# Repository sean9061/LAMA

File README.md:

# LAMA

LAMA は、左右分割・トラックボール付きのワイヤレス自作キーボードです。[roBa](https://github.com/kumamuk-git/roBa)（[keyball](https://github.com/Yowkees/keyball/) に影響を受けた分割キーボード）を改造して作りました。ファームウェアは [ZMK](https://zmk.dev/) です。

## 特徴

- **左右分割・カラムスタッガード配列。** roBa の両端（小指側）に1列ずつキーを増やしている
- **右手に 25mm のトラックボール**（センサーは PMW3610）。ボールを動かすとマウスのレイヤーに自動で切り替わる
- **Bluetooth（BLE）で無線接続。** マイコンは左右とも Seeed Studio XIAO nRF52840 Plus
- **単3電池1本で動く。** 昇圧回路（TPS61221）で 3.3V にしている。電源スイッチ付き。電池の残量はファームウェアからは測れない
- 左手にロータリーエンコーダ（EC12）を付けられる（押し込みスイッチは未配線）
- **ZMK Studio に対応。** 右手を USB でつなぐと、ブラウザからキーマップを変えられる
- XIAO の RGB LED で Bluetooth の接続状態を表示する
- キーマップは Mac で使う前提（英数/かな、⌘、Mission Control、Spotlight など）

## キーマップ

| レイヤー | 入り方 | 内容 |
|---|---|---|
| BASE | — | 文字の入力 |
| FUNCTION | 右手親指の ⏎ を長押し | F1〜F13、明るさ・音楽・音量、スクリーンショット（⇧⌘4 / ⇧⌘5） |
| NUM | 左手親指の Space を長押し | テンキー（左手）と記号（右手） |
| ARROW | 左手親指の かな を長押し | 矢印・Home/End、タブの切り替え、ブラウザの戻る/進む |
| MOUSE | トラックボールを動かす（自動） | 右手の J/K/L が左/中/右クリック |
| SCROLL | I を長押し | トラックボールでスクロール |
| SYSTEM | 左手親指の 英数 を長押し | Bluetooth の接続先の切り替え・消去、ブートローダー |

英数・かな のキーは、タップすると BASE レイヤーに戻ってから英数・かなを送ります。キーマップの詳しい説明とピン配置は [doc/firmware.md](doc/firmware.md) にあります。

[doc/keymap.html](doc/keymap.html) は、ダウンロードしてブラウザで開くと、押したキーが光る配置図です（`python3 doc/keymap_gen.py` で keymap から作り直せます）。

## ファームウェア

### 入手する

push すると、GitHub Actions がファームウェアをビルドします（[.github/workflows/build.yml](.github/workflows/build.yml)）。Actions のページで最新の実行を開き、Artifacts からダウンロードすると、次の3つが入っています。

| ファイル | 書き込む先 |
|---|---|
| `LAMA_R-seeeduino_xiao_ble-zmk.uf2` | 右手（central。トラックボール側） |
| `LAMA_L-seeeduino_xiao_ble-zmk.uf2` | 左手（peripheral） |
| `settings_reset-seeeduino_xiao_ble-zmk.uf2` | 左右の接続をやり直したいとき（下記） |

自分のキーマップでビルドしたいときは、このリポジトリを fork して `config/LAMA.keymap` を書き換え、fork 先で Actions を有効にしてください。

### 書き込む

1. XIAO を USB でパソコンにつなぎ、リセットボタンをすばやく2回押す
2. USB ドライブが出てくるので、uf2 をそこへコピーする。コピーが終わると自動で再起動する
3. もう片方も同じように書き込む

左右がつながらなくなったときは、左右それぞれに `settings_reset` を書き込んでから、もう一度 `LAMA_L` / `LAMA_R` を書き込みます。パソコン側に残っている Bluetooth の登録も削除してください。

### キーマップを変える

- **ZMK Studio を使う:** 右手を USB でつなぎ、[ZMK Studio](https://zmk.studio/) で変える。変更はキーボードに保存され、ファームウェアのキーマップより優先される
- **ファイルを書き換える:** `config/LAMA.keymap` を編集して push する。Studio で保存したキーマップが残っていると反映されないので、そのときは Studio で「Restore Stock Settings」を実行する

キー配置図（`keymap-drawer/`）は、Actions の「Draw Keymap」を手動で実行すると作り直されます。

## ハードウェア

| ディレクトリ | 内容 |
|---|---|
| `pcb/v2/roBa_L/`・`pcb/v2/roBa_R/` | LAMA の基板（KiCad、左手・右手）。roBa の v2 基板をもとに、増設した列・XIAO nRF52840 Plus・昇圧回路を加えている |
| `pcb/` のそのほか | `pcb/v1/` は roBa の旧版の基板。PMW3610 のブレークアウト基板、エンコーダの延長基板、シンボルとフットプリントのライブラリ（`_kicad_symbols/`・`_kicad_footprints/`・`KiCADv6/`） |

組み立ての手順とケースは、roBa 本家の[ビルドガイド](https://github.com/kumamuk-git/roBa/blob/main/doc/v3/buildguide_v3.md)と[ケースのデータ](https://github.com/kumamuk-git/roBa/tree/main/case)を参考にしてください。LAMA で足した部品（増設した列のスイッチ、昇圧回路、単3電池の端子）は、このガイドには載っていません。

KiCad でライブラリを読むには、環境変数 `ROBA_FP`（`pcb/_kicad_footprints`）、`ROBA_SYMBOL`（`pcb/_kicad_symbols`）、`ROBA_V6_FP`（`pcb/KiCADv6/footprints.pretty`）、`ROBA_V6_SYM`（`pcb/KiCADv6`）を設定してください（KiCad の「設定 → パスの設定」）。

## リポジトリの構成

```
.
├── boards/shields/LAMA/   ZMK のシールド定義(ピン配置・物理レイアウト・左右の設定)
├── config/                キーマップ(LAMA.keymap)・物理レイアウト(LAMA.json)・west.yml
├── keymap-drawer/         キー配置図(LAMA.svg)
├── doc/keymap.html        押したキーが光るキー配置図(doc/keymap_gen.py で生成)
├── build.yaml             GitHub Actions でビルドする組み合わせ
├── pcb/                   基板(上記)
├── doc/                   ファームウェアの説明・写真
└── zephyr/module.yml      このリポジトリを ZMK のモジュールとして読ませる設定
```

## クレジット

- [roBa](https://github.com/kumamuk-git/roBa)（kumamuk-git）— LAMA のもとになったキーボード。LAMA の基板・ファームウェアの設定・フットプリントとシンボルのライブラリは roBa のものを改造している。組み立てとケースも roBa 本家の資料を参照
- [keyball](https://github.com/Yowkees/keyball/) — roBa が影響を受けたキーボード
- [zmk-config-roBa](https://github.com/kumamuk-git/zmk-config-roBa) / [zmk-pmw3610-driver](https://github.com/kumamuk-git/zmk-pmw3610-driver) — ZMK の設定とトラックボールのドライバ
- [zmk-rgbled-widget](https://github.com/caksoylar/zmk-rgbled-widget) — XIAO の LED で接続状態を表示する
- [keymap-drawer](https://github.com/caksoylar/keymap-drawer) — キー配置図の生成

## ライセンス

[GPLv3](LICENSE)。[roBa](https://github.com/kumamuk-git/roBa)（GPLv3）をもとにした派生プロジェクトです。

## English

LAMA is a wireless split keyboard with a 25 mm trackball, based on [roBa](https://github.com/kumamuk-git/roBa). It adds an extra pinky column on each side, has a power switch and an optional EC12 rotary encoder on the left half, runs [ZMK](https://zmk.dev/) on two Seeed Studio XIAO nRF52840 Plus boards, is powered by a single AA battery per half, and supports ZMK Studio. GitHub Actions builds the firmware on every push. See [doc/firmware.md](doc/firmware.md) for the pin assignments and keymap details. Licensed under GPLv3.

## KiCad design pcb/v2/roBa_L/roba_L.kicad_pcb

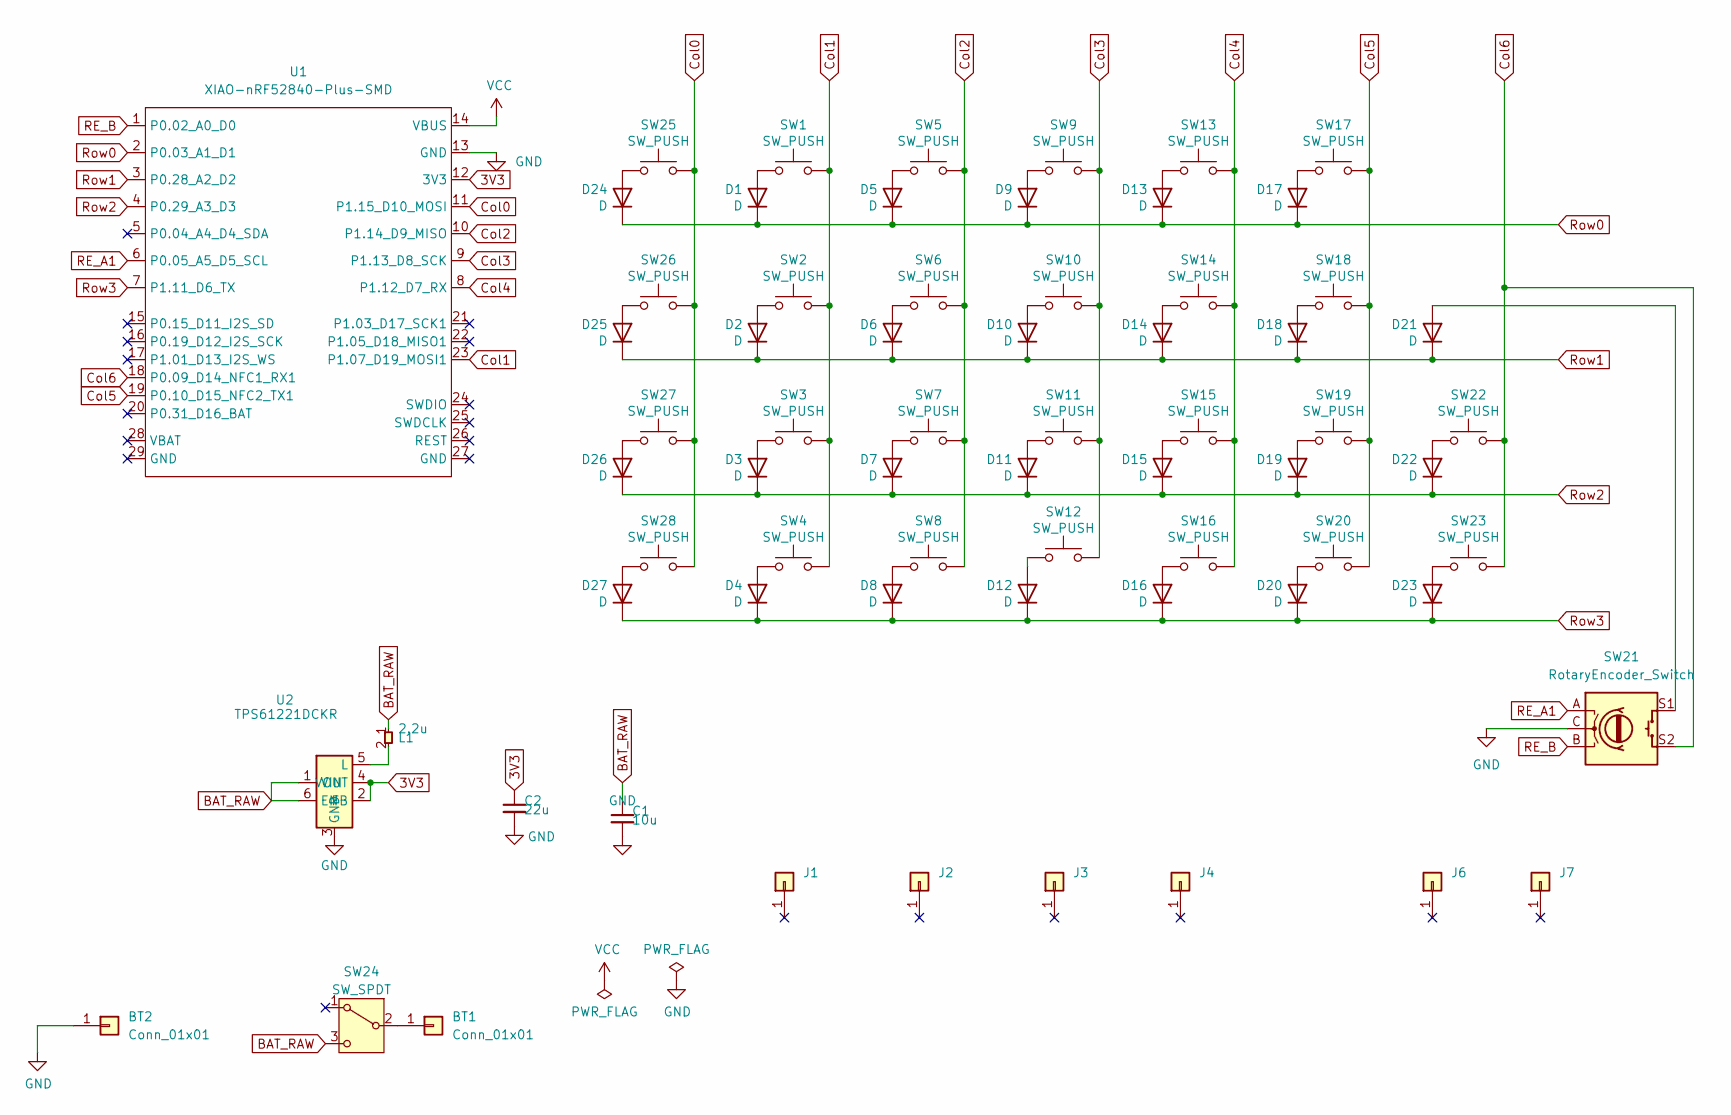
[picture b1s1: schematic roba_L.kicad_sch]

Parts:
BT1, BT2: Conn_01x01; BatteryLead_Plus
C1: 10u; C_0805_2012Metric
C2: 22u; C_0805_2012Metric
D1, D2, D3, D4, D5, D6, D7, D8, D9, D10, D11, D12, D13, D14, D15, D16, D17, D18, D19, D20, D21, D22, D23, D24, D25, D26, D27: D; Diode_SMD
J1, J2, J3, J4, J6, J7: Conn_01x01-Connector_Generic; MountingHole_4.3mm_M4
L1: 2.2u; C_0805_2012Metric
SW1, SW2, SW3, SW4, SW5, SW6, SW7, SW8, SW9, SW10, SW11, SW12, SW13, SW14, SW15, SW16, SW17, SW18, SW19, SW20, SW22, SW23, SW25, SW26, SW27, SW28: SW_PUSH; SW_MX_Choc
SW21: RotaryEncoder_Switch; SW_MX_EC12
SW24: SW_SPDT; TGSW_MSK-12D19
U1: XIAO-nRF52840-Plus-SMD
U2: TPS61221DCKR; DCK0006A

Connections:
3V3: C2.1, U1.12 (3V3), U2.2 (FB), U2.4 (VOUT)
BAT_RAW: C1.1, L1.1, SW24.3 (C), U2.1 (VIN), U2.6 (EN)
Col0: SW25.1, SW26.1, SW27.1, SW28.1, U1.11 (P1.15_D10_MOSI)
Col1: SW1.1, SW2.1, SW3.1, SW4.1, U1.23 (P1.07_D19_MOSI1)
Col2: SW5.1, SW6.1, SW7.1, SW8.1, U1.10 (P1.14_D9_MISO)
Col3: SW9.1, SW10.1, SW11.1, SW12.1, U1.9 (P1.13_D8_SCK)
Col4: SW13.1, SW14.1, SW15.1, SW16.1, U1.8 (P1.12_D7_RX)
Col5: SW17.1, SW18.1, SW19.1, SW20.1, U1.19 (P0.10_D15_NFC2_TX1)
Col6: SW21.S2, SW22.1, SW23.1, U1.18 (P0.09_D14_NFC1_RX1)
GND: BT2.1 (Pin_1_1), C1.2, C2.2, SW21.C, U1.13 (GND), U2.3 (GND)
unnamed: BT1.1 (Pin_1_1), SW24.2 (B)
unnamed: D1.2 (A), SW1.2
unnamed: D2.2 (A), SW2.2
unnamed: D3.2 (A), SW3.2
unnamed: D4.2 (A), SW4.2
unnamed: D5.2 (A), SW5.2
unnamed: D6.2 (A), SW6.2
unnamed: D7.2 (A), SW7.2
unnamed: D8.2 (A), SW8.2
unnamed: D9.2 (A), SW9.2
unnamed: D10.2 (A), SW10.2
unnamed: D11.2 (A), SW11.2
unnamed: D12.2 (A), SW12.2
unnamed: D13.2 (A), SW13.2
unnamed: D14.2 (A), SW14.2
unnamed: D15.2 (A), SW15.2
unnamed: D16.2 (A), SW16.2
unnamed: D17.2 (A), SW17.2
unnamed: D18.2 (A), SW18.2
unnamed: D19.2 (A), SW19.2
unnamed: D20.2 (A), SW20.2
unnamed: D21.2 (A), SW21.S1
unnamed: D22.2 (A), SW22.2
unnamed: D23.2 (A), SW23.2
unnamed: D24.2 (A), SW25.2
unnamed: D25.2 (A), SW26.2
unnamed: D26.2 (A), SW27.2
unnamed: D27.2 (A), SW28.2
unnamed: L1.2, U2.5 (L)
RE_A1: SW21.A, U1.6 (P0.05_A5_D5_SCL)
RE_B: SW21.B, U1.1 (P0.02_A0_D0)
Row0: D1.1 (K), D5.1 (K), D9.1 (K), D13.1 (K), D17.1 (K), D24.1 (K), U1.2 (P0.03_A1_D1)
Row1: D2.1 (K), D6.1 (K), D10.1 (K), D14.1 (K), D18.1 (K), D21.1 (K), D25.1 (K), U1.3 (P0.28_A2_D2)
Row2: D3.1 (K), D7.1 (K), D11.1 (K), D15.1 (K), D19.1 (K), D22.1 (K), D26.1 (K), U1.4 (P0.29_A3_D3)
Row3: D4.1 (K), D8.1 (K), D12.1 (K), D16.1 (K), D20.1 (K), D23.1 (K), D27.1 (K), U1.7 (P1.11_D6_TX)
VCC: U1.14 (VBUS)

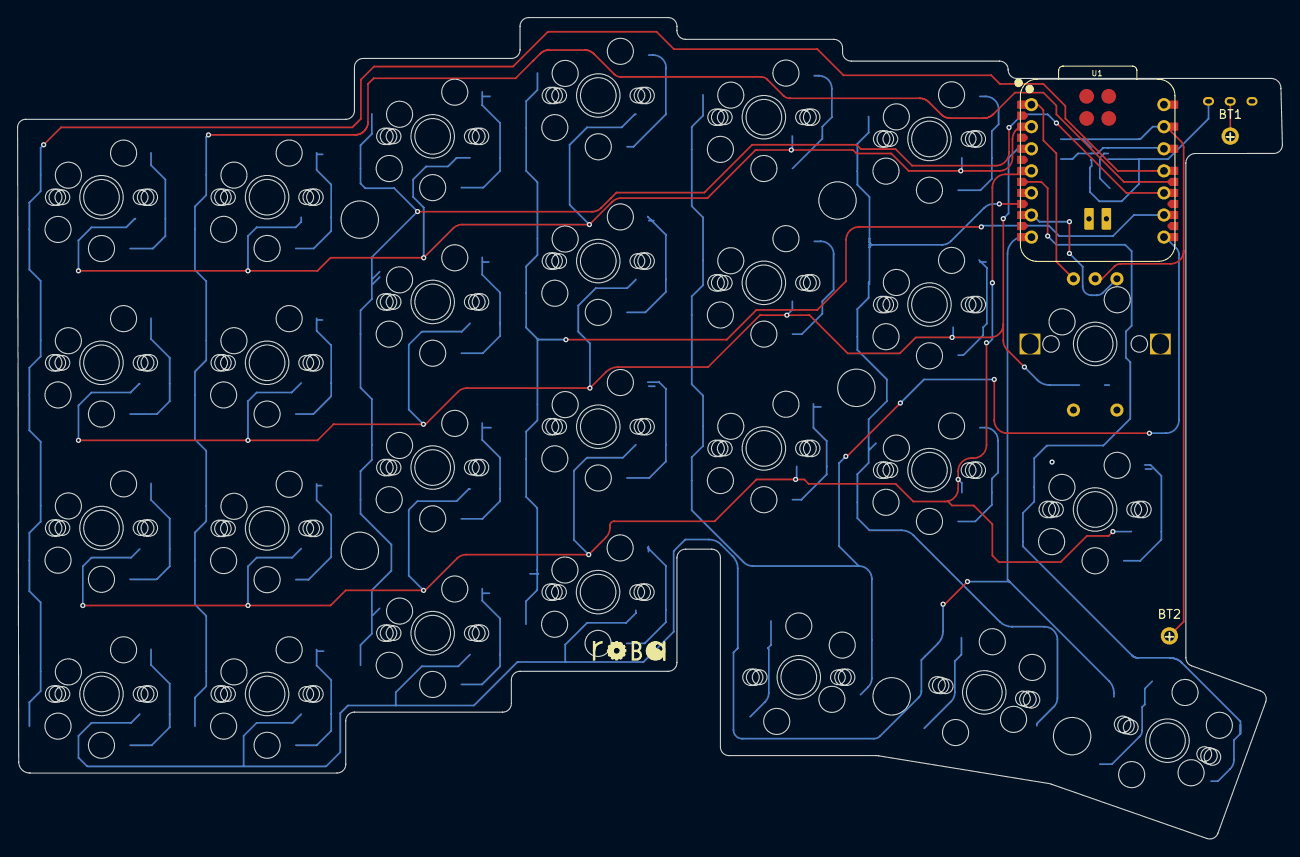
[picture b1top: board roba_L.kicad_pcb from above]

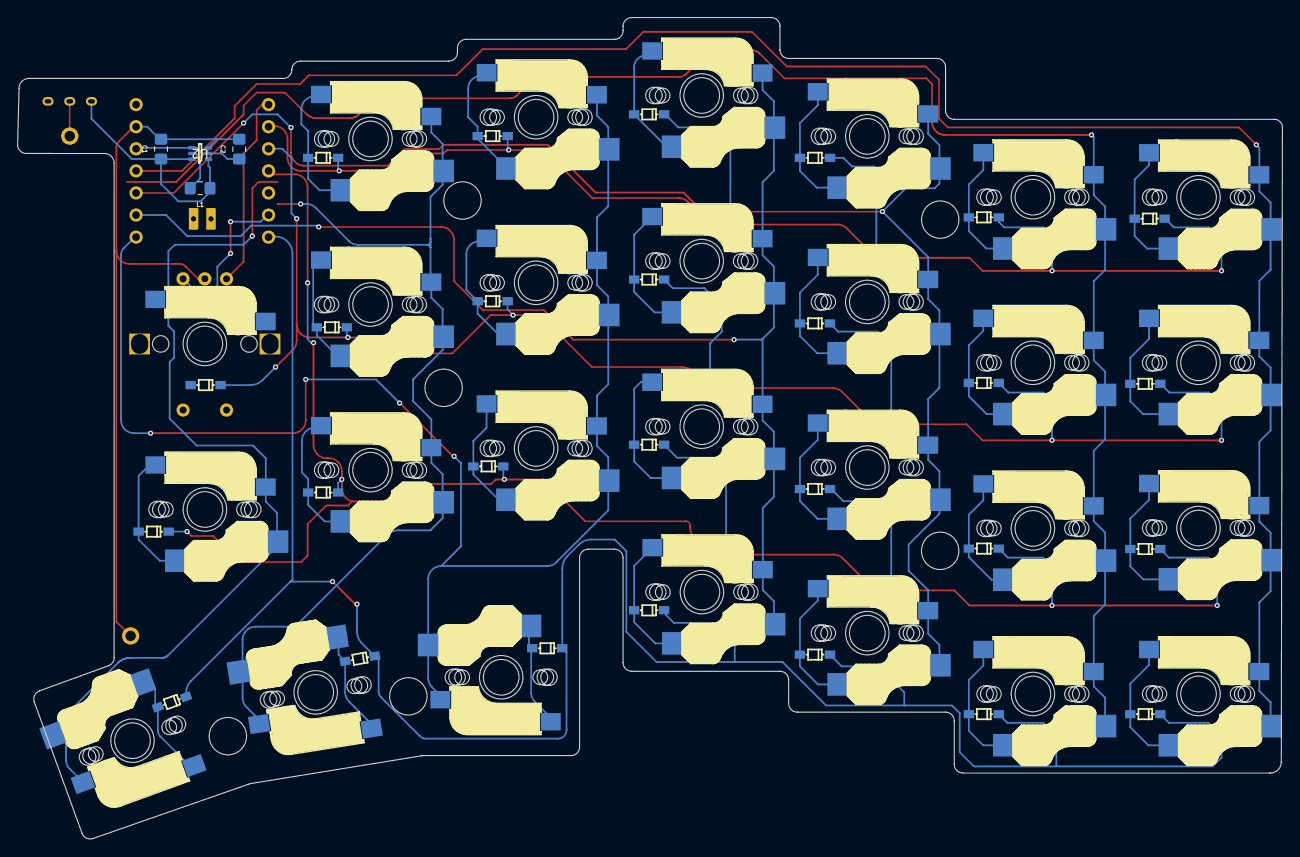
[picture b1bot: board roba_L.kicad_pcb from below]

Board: 2 copper layers, 145.5 x 94.5 mm, 68 parts (5 on the bottom side), 44 nets.

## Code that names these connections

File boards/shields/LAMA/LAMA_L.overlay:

#include "LAMA.dtsi"

&kscan0 {
        col-gpios  // PCBのCol0-Col6の順
            = <&xiao_d 10 GPIO_ACTIVE_HIGH>   // Col0 増設列 (D10)
            , <&gpio1 7 GPIO_ACTIVE_HIGH>     // Col1 (P1.07 / D19)
            , <&xiao_d 9 GPIO_ACTIVE_HIGH>    // Col2
            , <&xiao_d 8 GPIO_ACTIVE_HIGH>    // Col3
            , <&xiao_d 7 GPIO_ACTIVE_HIGH>    // Col4
            , <&gpio0 10 GPIO_ACTIVE_HIGH>    // Col5 (P0.10 / D15)
            , <&gpio0 9 GPIO_ACTIVE_HIGH>     // Col6 (P0.09 / D14)
            ;
};

&left_encoder {
    status = "okay";
};
